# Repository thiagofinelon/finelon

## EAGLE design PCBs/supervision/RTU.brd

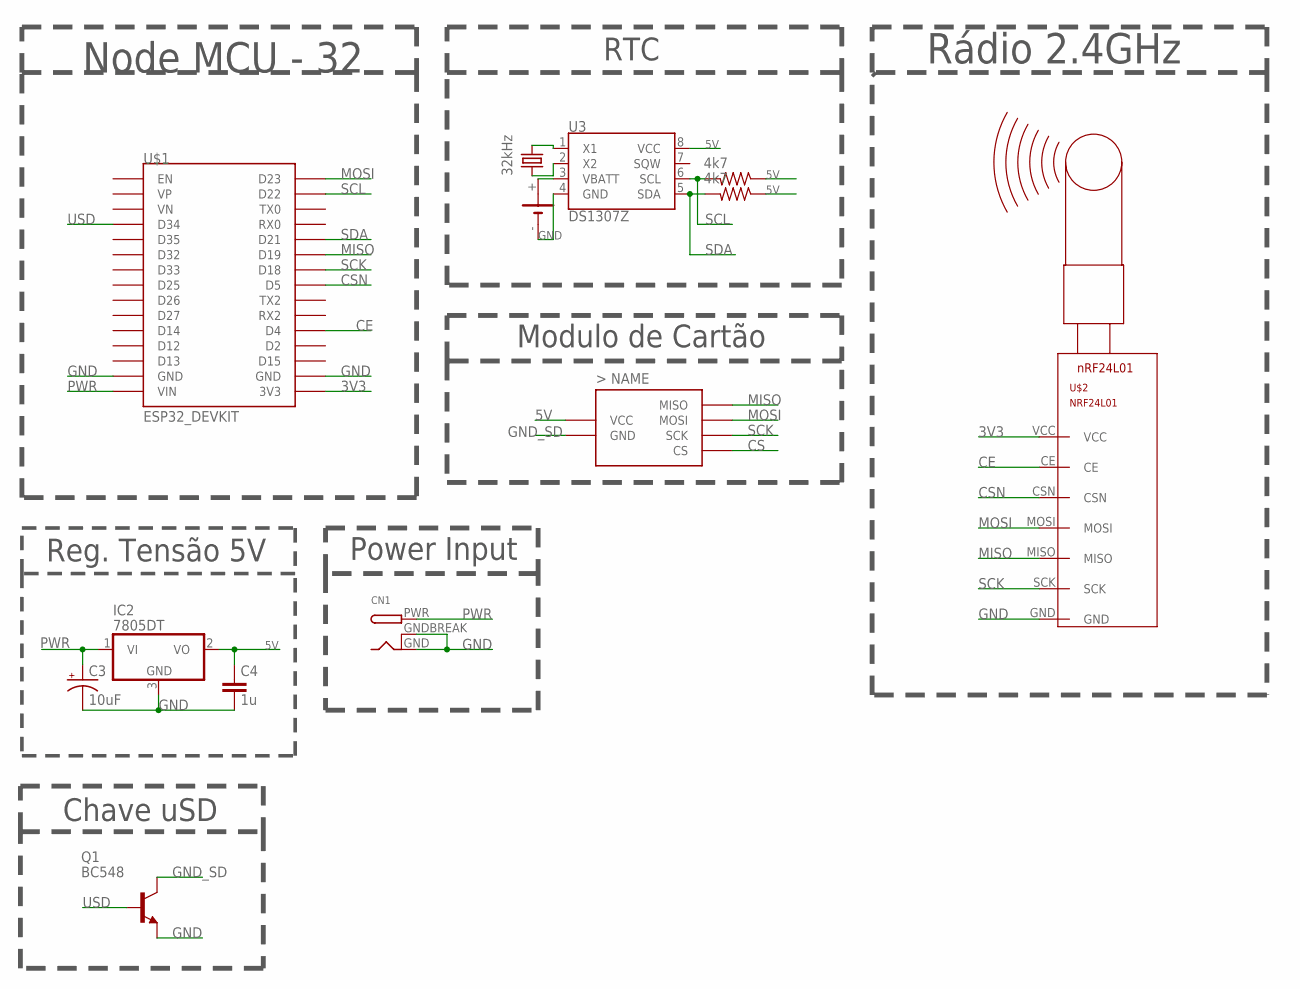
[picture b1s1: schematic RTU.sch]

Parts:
C3: 10uF; CPOL-RADIAL-2.5MM-5MM
C4: 1u; C025-024X044
CN1: DCBARRELPTH; DCJACK_2MM_PTH
G2: CH291-1220LF
IC2: 7805DT; TO252
Q1: BC548; TO92-EBC
R4, R5: 4k7; 0204/7
U2: MICROSD_CATALEX
U3: DS1307Z; SO08-0.15
U$1: ESP32_DEVKIT
U$2: NRF24L01
Y2: 32kHz; TC38H

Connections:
3V3: U$1.3V3, U$2.VCC
5V: C4.1, IC2.2 (VO), R4.1, R5.1, U2.VCC, U3.8 (VCC)
CE: U$1.D4, U$2.CE
CS: U2.CS
CSN: U$1.D5, U$2.CSN
GND: C3.2 (-), C4.2, CN1.GND, CN1.GNDBREAK, G2.-, IC2.3 (GND), Q1.E, U3.4 (GND), U$1.GND@1 (GND), U$1.GND@2 (GND), U$2.GND
GND_SD: Q1.C, U2.GND
MISO: U2.MISO, U$1.D19, U$2.MISO
MOSI: U2.MOSI, U$1.D23, U$2.MOSI
unnamed: U3.1 (X1), Y2.2
unnamed: U3.2 (X2), Y2.1
unnamed: G2.+, U3.3 (VBATT)
PWR: C3.1 (+), CN1.PWR, IC2.1 (VI), U$1.VIN
SCK: U2.SCK, U$1.D18, U$2.SCK
SCL: R4.2, U3.6 (SCL), U$1.D22
SDA: R5.2, U3.5 (SDA), U$1.D21
USD: Q1.B, U$1.D34

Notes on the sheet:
Power Input
Rádio 2.4GHz
Modulo de Cartão
RTC
Reg. Tensão 5V
Chave uSD
Node MCU - 32

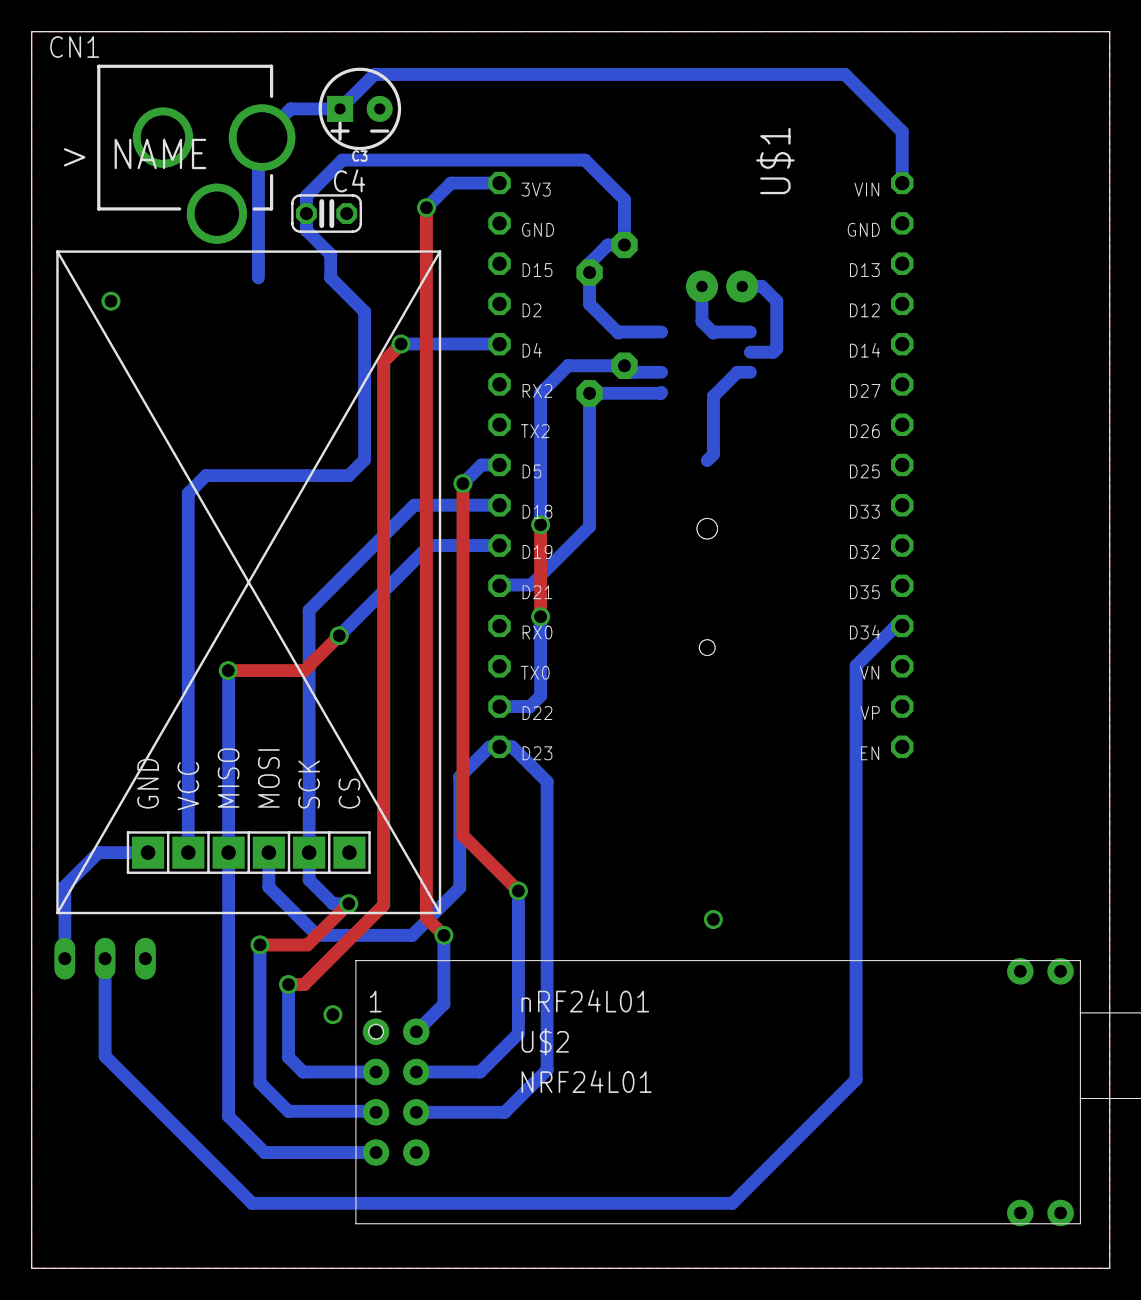
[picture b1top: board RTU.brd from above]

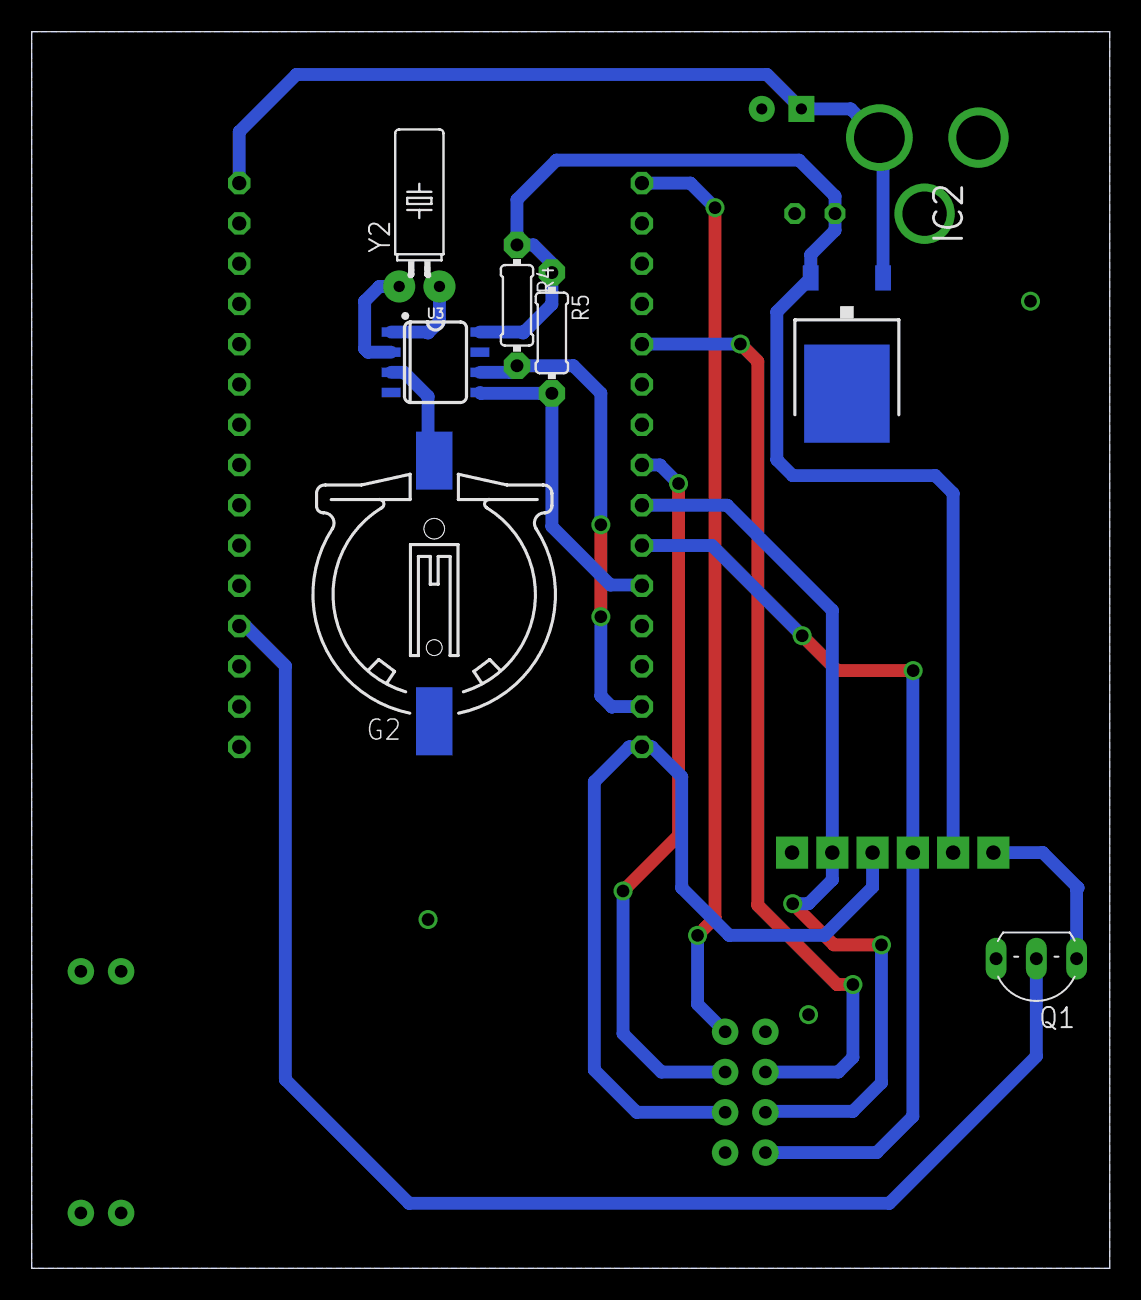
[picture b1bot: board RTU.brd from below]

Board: 2 copper layers, 68.0 x 78.0 mm, 13 parts (7 on the bottom side), 16 nets.

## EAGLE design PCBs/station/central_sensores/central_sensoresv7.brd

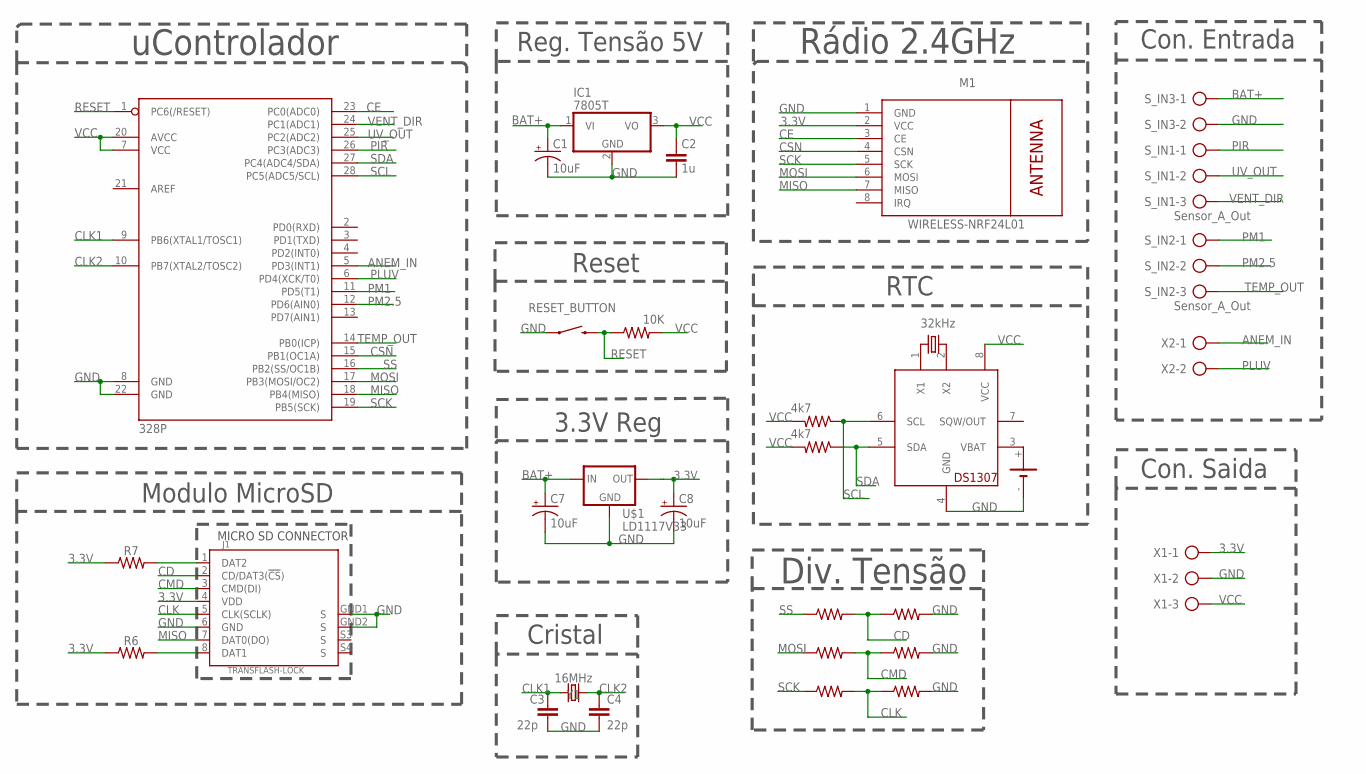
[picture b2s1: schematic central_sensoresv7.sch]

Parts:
C1, C7, C8: 10uF; CPOL-RADIAL-2.5MM-5MM
C2: 1u; C025-024X044
C3, C4: 22p; C2.5-3
G2: CH291-1220LF
IC1: 7805T; TO220H
IC2: DS1307; DIL08
J1: TRANSFLASH-LOCK; TRANSFLASH-LOCK-SOCK
M1: WIRELESS-NRF24L01
R1: 10K; 0204/7
R2, R3, R8, R9, R10, R11: R-US_0204/7; 0204/7
R4, R5: 4k7; 0204/7
R6, R7: 100k; 0204/7
RESET_BUTTON: MOMENTARY-SWITCH-SPST-PTH-6.0MM; TACTILE_SWITCH_PTH_6.0MM
S_IN1, S_IN2: Sensor_A_Out; AK500/3-H
S_IN3: Sensor_A_Out; AK500/2-H
U1: 328P; DIP28
U$1: LD1117V33
X1: AK500/3-H
X2: AK500/2-H
Y1: 16MHz; HC49US
Y2: 32kHz; TC38H

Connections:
3.3V: C8.1 (+), J1.4 (VDD), M1.2 (VCC), R6.1, R7.1, U$1.OUT, X1.1
ANEM_IN: U1.5 (PD3(INT1)), X2.1
BAT+: C1.1 (+), C7.1 (+), IC1.1 (VI), S_IN3.1, U$1.IN
CD: J1.2 (CD/DAT3(!CS!)), R2.2, R3.1
CE: M1.3 (CE), U1.23 (PC0(ADC0))
CLK: J1.5 (CLK(SCLK)), R10.2, R11.1
CLK1: C3.1, U1.9 (PB6(XTAL1/TOSC1)), Y1.2
CLK2: C4.1, U1.10 (PB7(XTAL2/TOSC2)), Y1.1
CMD: J1.3 (CMD(DI)), R8.2, R9.1
CSN: M1.4 (CSN), U1.15 (PB1(OC1A))
GND: C1.2 (-), C2.2, C3.2, C4.2, C7.2 (-), C8.2 (-), G2.-, IC1.2 (GND), IC2.4 (GND), J1.6 (GND), J1.GND1 (S), J1.GND2 (S), M1.1 (GND), R3.2, R9.2, R11.2, RESET_BUTTON.1, S_IN3.2, U1.8 (GND), U1.22 (GND), U$1.GND, X1.2
MISO: J1.7 (DAT0(DO)), M1.7 (MISO), U1.18 (PB4(MISO))
MOSI: M1.6 (MOSI), R8.1, U1.17 (PB3(MOSI/OC2))
unnamed: IC2.2 (X2), Y2.2
unnamed: IC2.1 (X1), Y2.1
unnamed: G2.+, IC2.3 (VBAT)
unnamed: J1.8 (DAT1), R6.2
unnamed: J1.1 (DAT2), R7.2
PIR: S_IN1.1, U1.26 (PC3(ADC3))
PLUV: U1.6 (PD4(XCK/T0)), X2.2
PM1: S_IN2.1, U1.11 (PD5(T1))
PM2.5: S_IN2.2, U1.12 (PD6(AIN0))
RESET: R1.1, RESET_BUTTON.3 (2), U1.1 (PC6(/RESET))
SCK: M1.5 (SCK), R10.1, U1.19 (PB5(SCK))
SCL: IC2.6 (SCL), R4.1, U1.28 (PC5(ADC5/SCL))
SDA: IC2.5 (SDA), R5.1, U1.27 (PC4(ADC4/SDA))
SS: R2.1, U1.16 (PB2(SS/OC1B))
TEMP_OUT: S_IN2.3, U1.14 (PB0(ICP))
UV_OUT: S_IN1.2, U1.25 (PC2(ADC2))
VCC: C2.1, IC1.3 (VO), IC2.8 (VCC), R1.2, R4.2, R5.2, U1.7 (VCC), U1.20 (AVCC), X1.3
VENT_DIR: S_IN1.3, U1.24 (PC1(ADC1))

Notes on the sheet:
Reg. Tensão 5V
Cristal
RTC
Reset
uControlador
Rádio 2.4GHz
Con. Entrada
Con. Saida
3.3V Reg
MICRO SD CONNECTOR
Div. Tensão
Modulo MicroSD

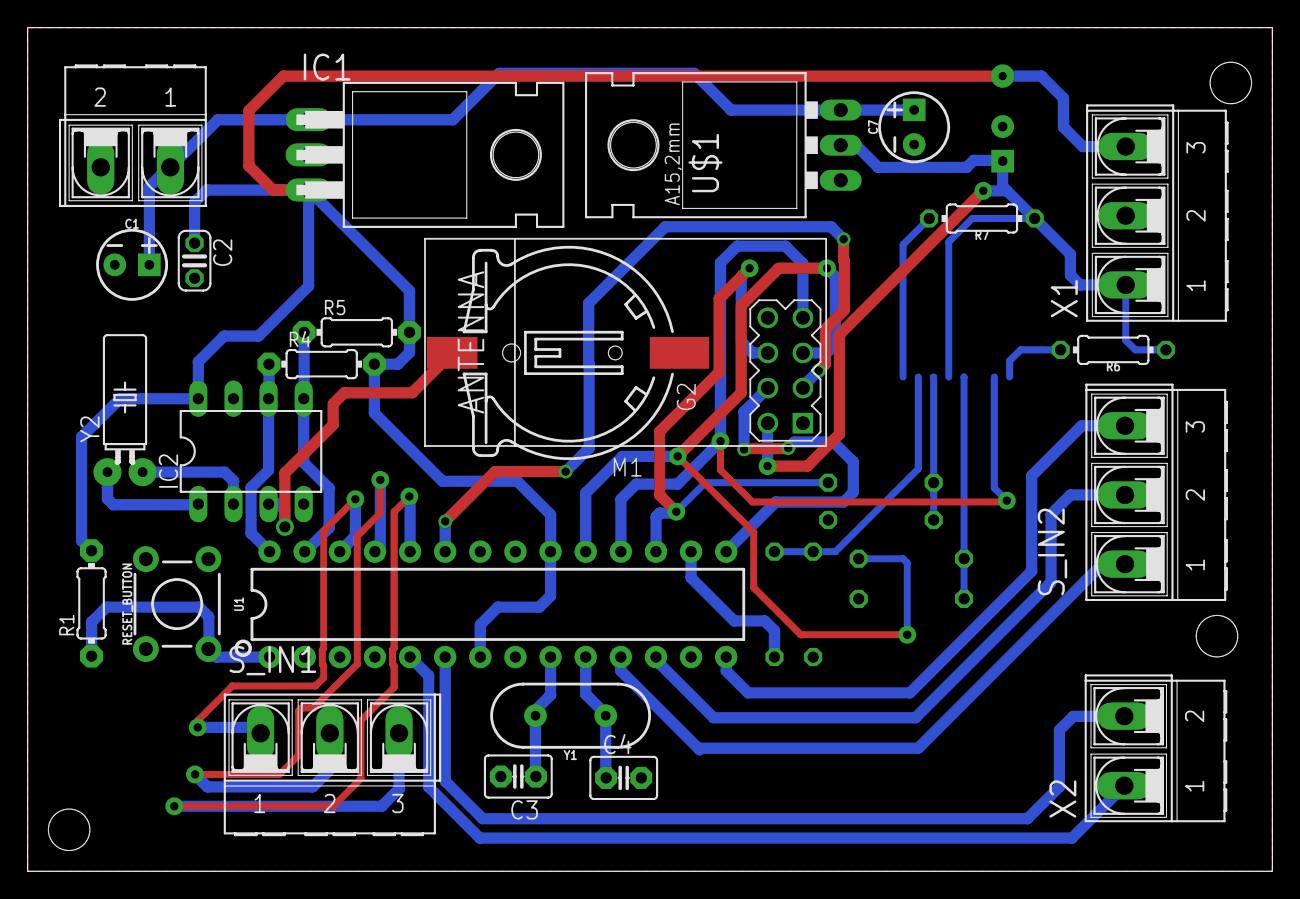
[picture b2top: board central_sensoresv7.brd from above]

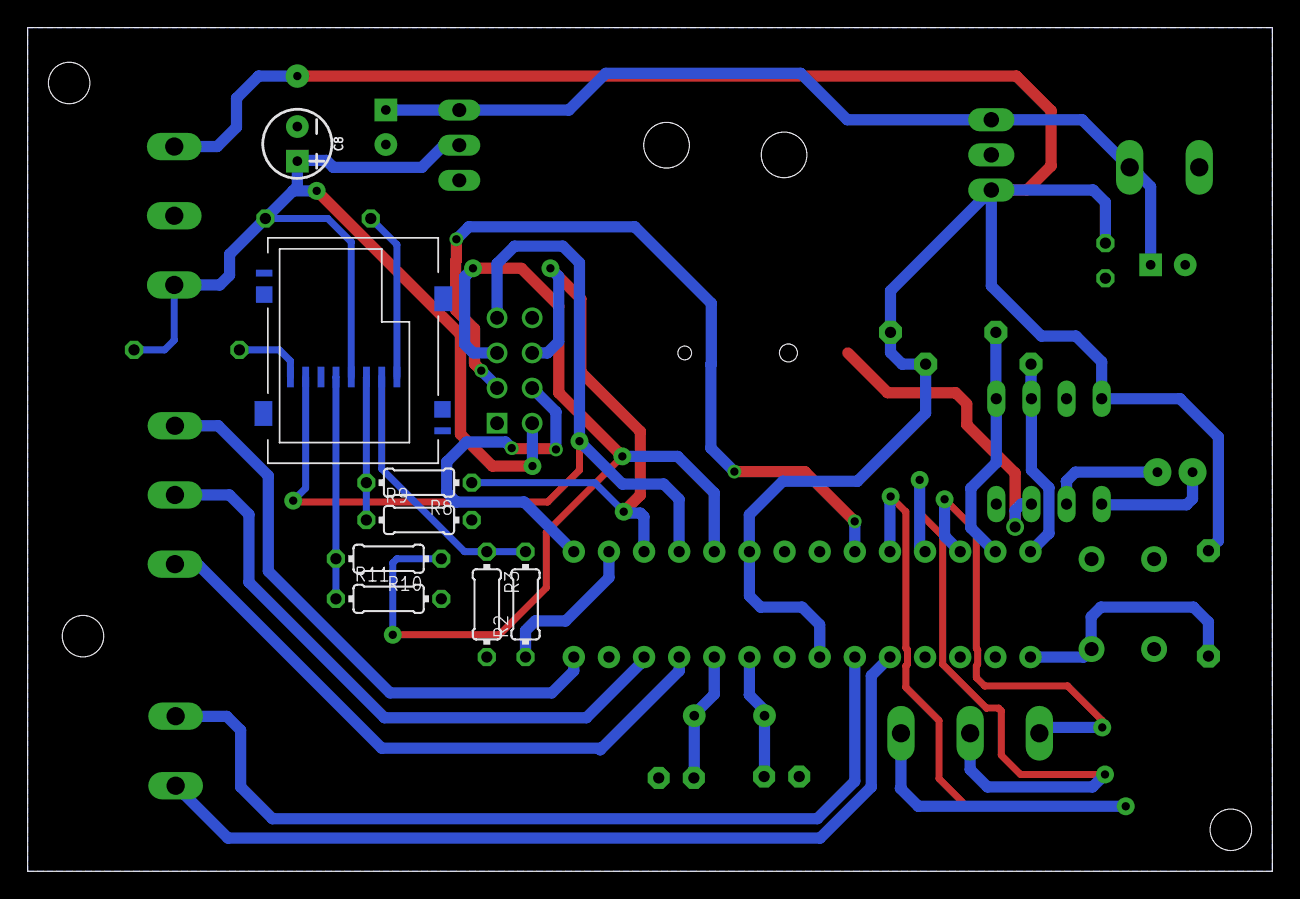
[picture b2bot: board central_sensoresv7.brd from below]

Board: 2 copper layers, 90.0 x 61.0 mm, 32 parts (8 on the bottom side), 31 nets.

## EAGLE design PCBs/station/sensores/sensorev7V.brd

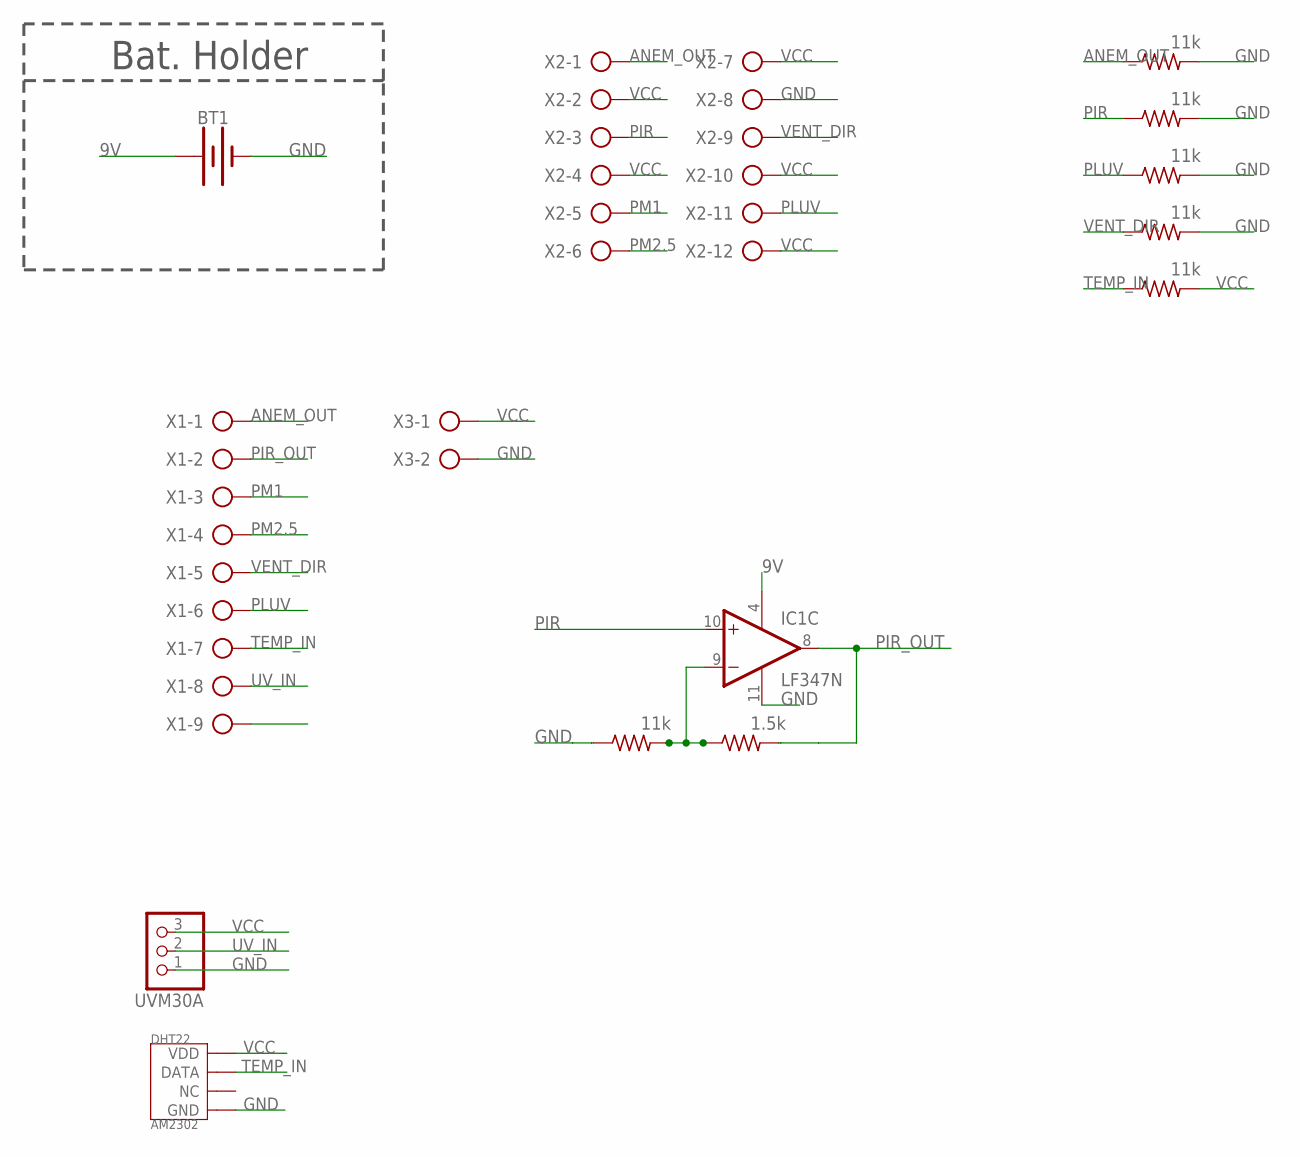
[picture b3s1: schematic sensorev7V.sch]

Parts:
BT1: BATTERY-9V; BATTCON_9V
DHT22: AM2302; SNR4-2.54-25.0X15.0X7.0MM
IC1: LF347N; DIL14
R1, R3, R4, R5, R6, R7: 11k; 0204/7
R2: 1.5k; 0204/7
UVM30A: PINHD-1X3/90; 1X03/90
X1: AK500/9
X2: AK500/12
X3: AK500/2

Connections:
9V: BT1.+, IC1.4 (V+)
ANEM_OUT: R3.1, X1.1, X2.1
GND: BT1.-, DHT22.P$4 (GND), IC1.11 (V-), R1.1, R3.2, R4.2, R5.2, R6.2, UVM30A.1, X2.8, X3.2
unnamed: IC1.9 (-IN), R1.2, R2.1
PIR: IC1.10 (+IN), R4.1, X2.3
PIR_OUT: IC1.8 (OUT), R2.2, X1.2
PLUV: R5.1, X1.6, X2.11
PM1: X1.3, X2.5
PM2.5: X1.4, X2.6
TEMP_IN: DHT22.P$2 (DATA), R7.1, X1.7
UV_IN: UVM30A.2, X1.8
VCC: DHT22.P$1 (VDD), R7.2, UVM30A.3, X2.2, X2.4, X2.7, X2.10, X2.12, X3.1
VENT_DIR: R6.1, X1.5, X2.9

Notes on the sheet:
Bat. Holder

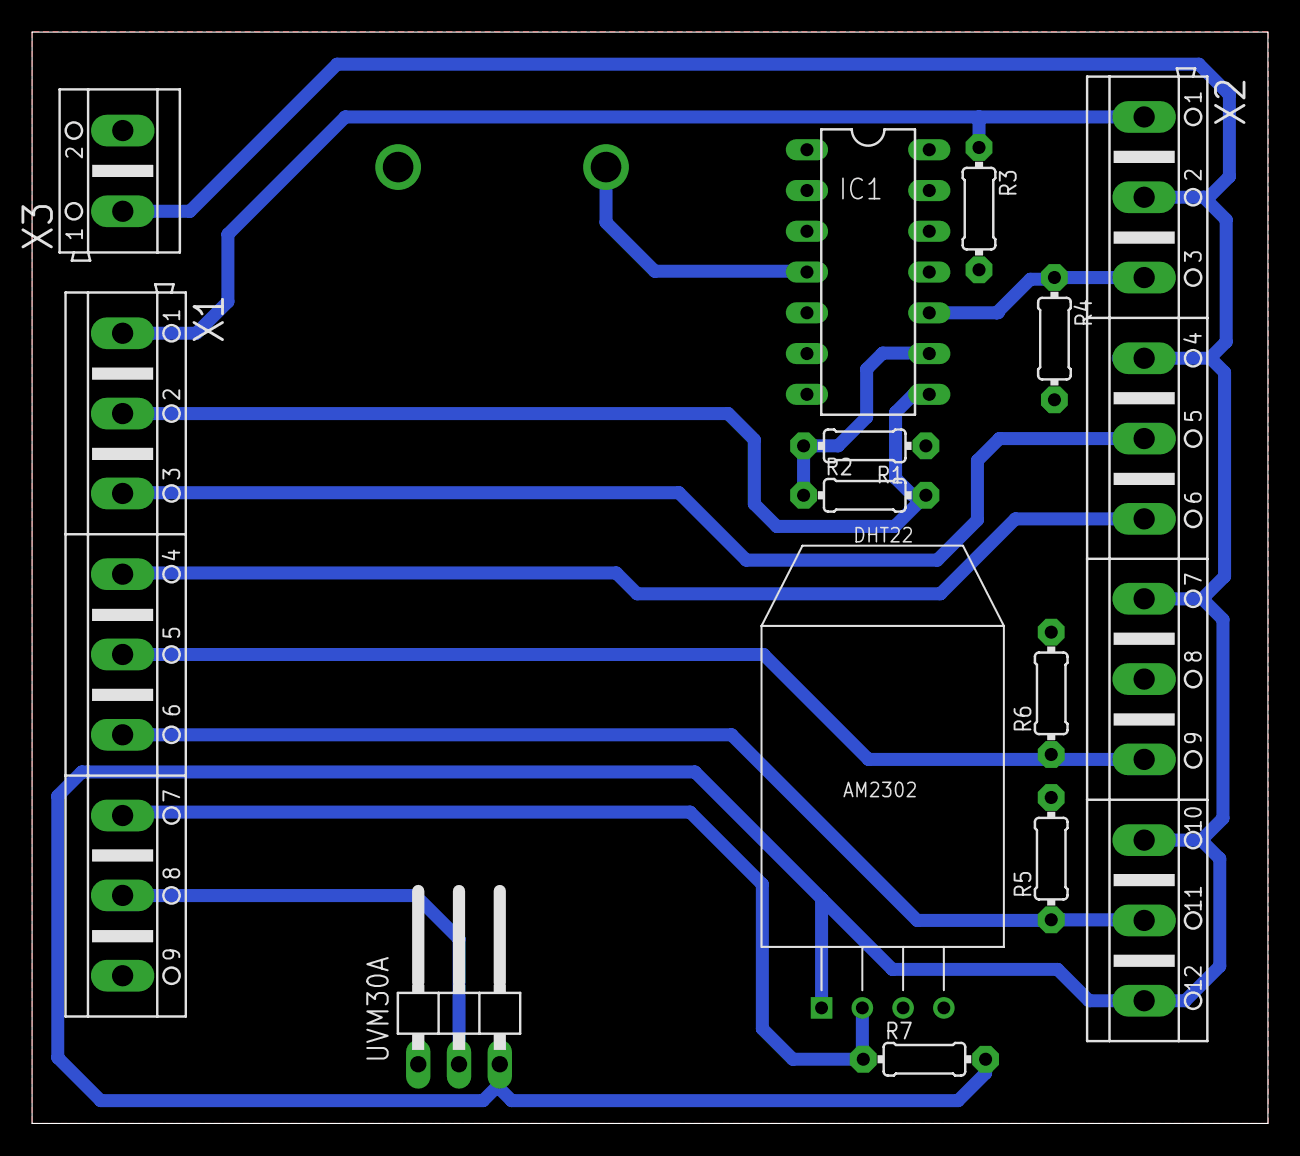
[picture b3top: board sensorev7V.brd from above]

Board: 2 copper layers, 77.0 x 68.0 mm, 14 parts (1 on the bottom side), 13 nets.

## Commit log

2019-01-19 Backup
2019-01-23 Atualização com correção da leitura dos sensores.
2019-01-23 Desfazendo caca
2019-01-24 Case e tampa do sistema supervisorio
2019-01-24 Alterações na PCB do sistema supervisorio
2019-02-01 Adição de suporte para parafusos na case da RTU
2019-02-01 Adição de buracos para parafusos na PCB da RTU
2019-02-11 Re-prototipação da PCB do sistema supervisorio
2019-10-22 Removing files from master
2019-10-22 Adding branch dev

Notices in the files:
parts and their libraries:
SparkFun-Capacitors: Licensing: Creative Commons ShareAlike 4.0 International - https://creativecommons.org/licenses/by-sa/4.0
diy-modules: Released under the Creative Commons Attribution 4.0 International License: http://creativecommons.org/licenses/by/4.0
